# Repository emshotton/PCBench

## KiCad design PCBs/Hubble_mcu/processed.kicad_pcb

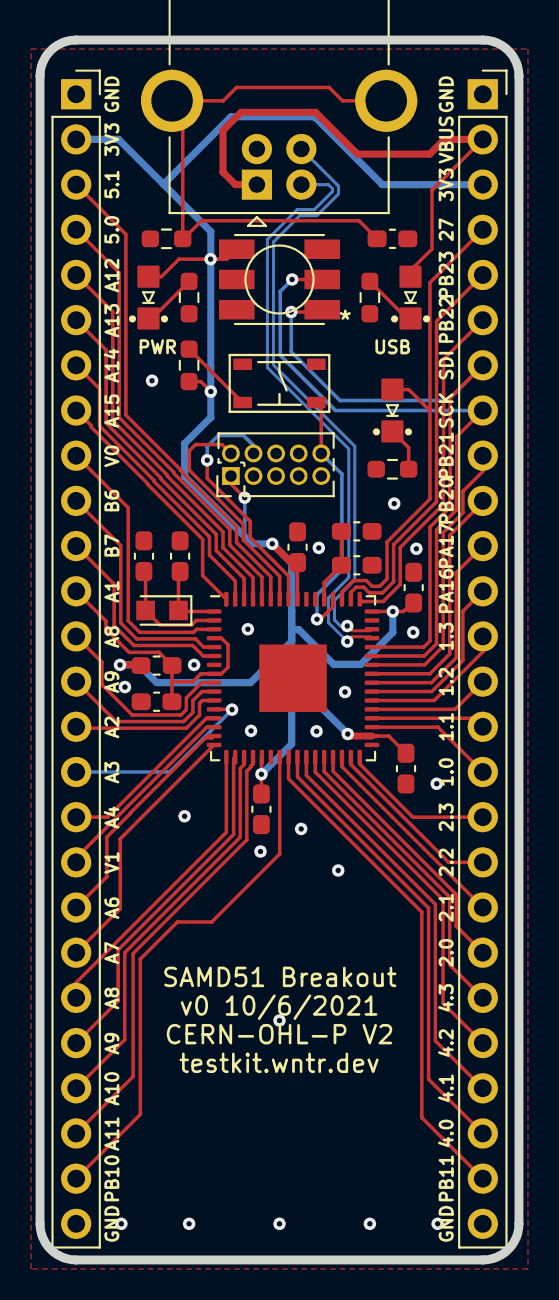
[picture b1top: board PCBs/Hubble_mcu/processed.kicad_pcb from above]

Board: 2 copper layers, 26.9 x 68.6 mm, 27 parts (0 on the bottom side), 60 nets.

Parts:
C1, C2: 18pF; C_0603_1608Metric_Pad1.08x0.95mm_HandSolder
C3: 4.7nF; C_0603_1608Metric_Pad1.08x0.95mm_HandSolder
C4, C5, C7, C8, C9, C10: 0.1uF; C_0603_1608Metric_Pad1.08x0.95mm_HandSolder
C6: 4.7uF; C_0603_1608Metric_Pad1.08x0.95mm_HandSolder
D1: POWER; LED_0805_Kingbright_APT2012
D2: USB; LED_0805_Kingbright_APT2012
D3: Dotstar; Dotstar_5050
D4: ACT; LED_0805_Kingbright_APT2012
FB1: 300mA; L_0603_1608Metric_Pad1.05x0.95mm_HandSolder
J1: USB_B_Receptacle; USB_B_OST_USB-B1HSxx_Horizontal
J2: SWD; PinHeader_2x05_P1.27mm_Vertical
J3, J4: Conn_01x26; PinSocket_1x26_P2.54mm_Vertical
R1, R2, R3, R4, R5: 10k; R_0603_1608Metric_Pad0.98x0.95mm_HandSolder
SW1: RESET; Tactile_Switch_4.2mm
U2: ATSAMD51J20A-M; QFN-64-1EP_9x9mm_P0.5mm_EP3.8x3.8mm
Y1: 32.768kHz; Crystal_SMD_2012-2Pin_2.0x1.2mm_HandSoldering

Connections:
+3V3: C7.1, C8.1, C9.1, C10.1, D1.2, D3.4, FB1.2, J2.1, J3.2, J4.3, R3.1, U2.21, U2.34, U2.48, U2.56
/ADC0.AIN1+ANAREF.VREF0: C4.1, FB1.1, J3.12, U2.4, U2.8
/ADC0.AIN2+ADC1.AIN0: J3.15, U2.11
/ADC0.AIN3+ADC1.AIN1: J3.16, U2.12
/ADC0.AIN4+ANAREF.VREF1: J3.17, U2.13
/ADC0.AIN6+ANAREF.VREF2: J3.19, U2.15
/ADC0.AIN7: J3.20, U2.16
/ADC0.AIN8+ADC1.AIN2: J3.21, U2.17
/ADC0.AIN9+ADC1.AIN3: J3.22, U2.18
/ADC0.AIN10: J3.23, U2.19
/ADC0.AIN11: J3.24, U2.20
/ADC0.AIN12: J3.5, U2.61
/ADC0.AIN13: J3.6, U2.62
/ADC0.AIN14: J3.7, U2.63
/ADC0.AIN15: J3.8, U2.64
/ADC1.AIN6: J3.10, U2.5
/ADC1.AIN7: J3.11, U2.6
/ADC1.AIN8: J3.13, U2.9
/ADC1.AIN9: J3.14, U2.10
/D+: J1.3, U2.46
/D-: J1.2, U2.45
/DAC.VOUT0: J3.9, U2.3
/DAC.VOUT1: J3.18, U2.14
/DOTSTAR_SCK: D3.2, J4.8, U2.43
/DOTSTAR_SDI: D3.1, J4.7, U2.44
/PA16: J4.12, U2.39
/PA17: J4.11, U2.40
/PA20: J4.10, U2.41
/PA21: J4.9, U2.42
/PA27: D4.2, J4.4, U2.51
/PB10: J3.25, U2.23
/PB11: J4.25, U2.24
/PB22: J4.6, U2.49
/PB23: J4.5, U2.50
/RESET: J2.10, R3.2, SW1.1, U2.52
/SERCOM1.0: J4.16, U2.35
/SERCOM1.1: J4.15, U2.36
/SERCOM1.2: J4.14, U2.37
/SERCOM1.3: J4.13, U2.38
/SERCOM2.0: J4.20, U2.29
/SERCOM2.1: J4.19, U2.30
/SERCOM2.2: J4.18, U2.31
/SERCOM2.3: J4.17, U2.32
/SERCOM4.0: J4.24, U2.25
/SERCOM4.1: J4.23, U2.26
/SERCOM4.2: J4.22, U2.27
/SERCOM4.3: J4.21, U2.28
/SERCOM5.0: J3.4, U2.60
/SERCOM5.1: J3.3, U2.59
/SWCLK: J2.4, U2.57
/SWDIO: J2.2, U2.58
/VBUS: D2.2, J1.1, J4.2
/VDDCORE: C5.1, C6.1, U2.53
/XIN: C1.1, U2.1, Y1.1
/XOUT: C2.1, U2.2, Y1.2
GND: C1.2, C2.2, C3.2, C4.2, C5.2, C6.2, C7.2, C8.2, C9.2, C10.2, D3.3, J1.4, J2.3, J2.5, J2.9, J3.1, J3.26, J4.1, J4.26, R1.2, R2.2, R4.2, R5.2, SW1.2, U2.7, U2.22, U2.33, U2.47, U2.54, U2.65
unnamed: C3.1, J1.5, R4.1
unnamed: D1.1, R1.1
unnamed: D2.1, R2.1
unnamed: D4.1, R5.1

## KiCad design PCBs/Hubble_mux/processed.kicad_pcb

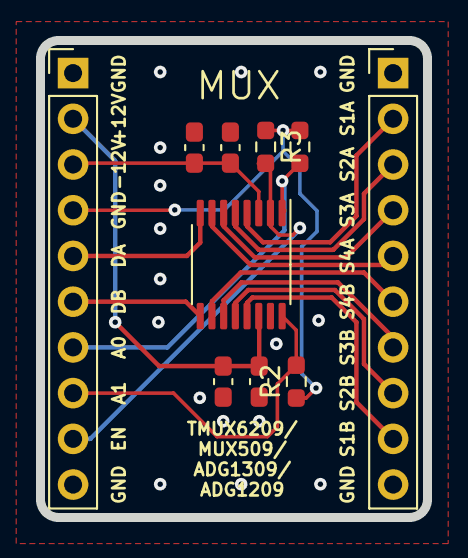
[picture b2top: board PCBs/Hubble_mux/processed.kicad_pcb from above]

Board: 2 copper layers, 21.5 x 26.5 mm, 10 parts (0 on the bottom side), 17 nets.

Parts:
C1, C3: 1uF; C_0603_1608Metric_Pad1.08x0.95mm_HandSolder
C2, C4: 0.1uF; C_0603_1608Metric_Pad1.08x0.95mm_HandSolder
J1: Left; PinHeader_1x10_P2.54mm_Vertical
J2: Right; PinHeader_1x10_P2.54mm_Vertical
R1, R2, R3: 10k; R_0603_1608Metric_Pad0.98x0.95mm_HandSolder
U1: TMUX6209; TSSOP-16_4.4x5mm_P0.65mm

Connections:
+3V3: J1.4, R1.1, R2.1, R3.1
+12V: C1.1, C2.1, J1.2, U1.14
-12V: C3.1, C4.1, J1.3, U1.3
/A0: J1.7, R1.2, U1.1
/A1: J1.8, R2.2, U1.16
/DA: J1.5, U1.8
/DB: J1.6, U1.9
/EN: J1.9, R3.2, U1.2
/S1A: J2.2, U1.4
/S1B: J2.9, U1.13
/S2A: J2.3, U1.5
/S2B: J2.8, U1.12
/S3A: J2.4, U1.6
/S3B: J2.7, U1.11
/S4A: J2.5, U1.7
/S4B: J2.6, U1.10
GND: C1.2, C2.2, C3.2, C4.2, J1.1, J1.10, J2.1, J2.10, U1.15

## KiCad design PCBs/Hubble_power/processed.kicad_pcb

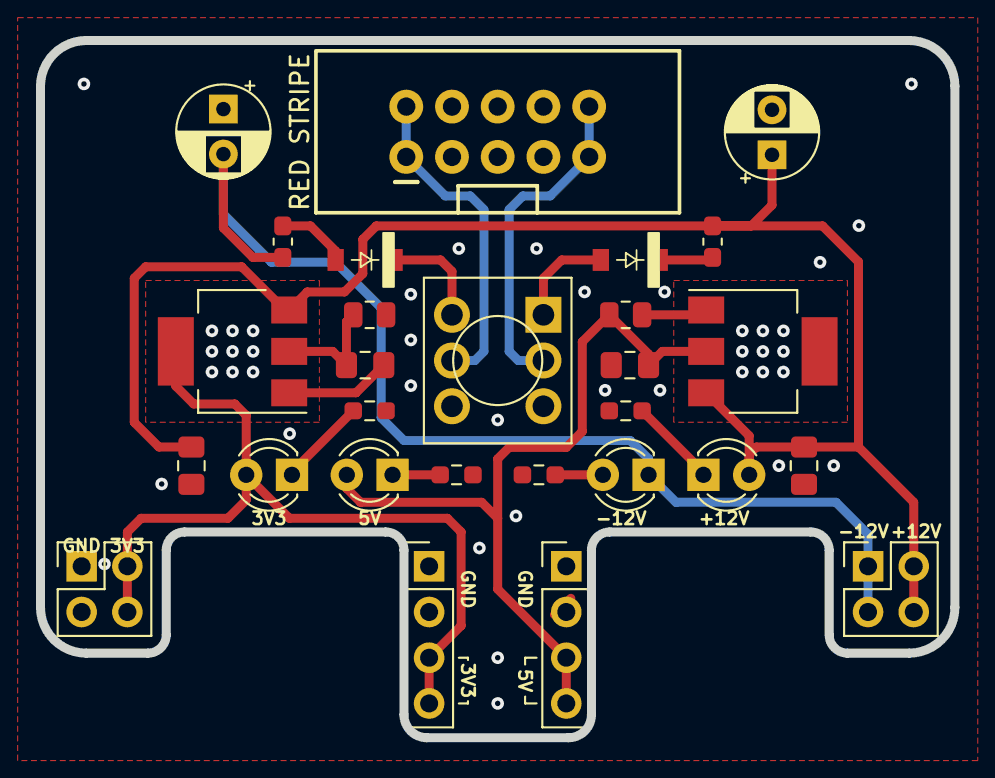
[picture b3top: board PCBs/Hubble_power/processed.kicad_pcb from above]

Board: 2 copper layers, 50.8 x 38.7 mm, 28 parts (0 on the bottom side), 15 nets.

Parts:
C1, C2, C3, C4: 10uF; C_0805_2012Metric_Pad1.18x1.45mm_HandSolder
C5, C6: 10uF; CP_Radial_D5.0mm_P2.50mm
D1, D2: BARRIER; D_SOD-123
D3: Blue; LED_D3.0mm
D4: Red; LED_D3.0mm
D5: Green; LED_D3.0mm
D6: Yellow; LED_D3.0mm
FB1, FB2: BEAD; L_0603_1608Metric_Pad1.05x0.95mm_HandSolder
J1: Eurorack_Power
J2: Left power; PinHeader_2x02_P2.54mm_Vertical
J3: Left; PinHeader_1x04_P2.54mm_Vertical
J4: Right; PinHeader_1x04_P2.54mm_Vertical
J5: Right power; PinHeader_2x02_P2.54mm_Vertical
R1, R2: 0.3-22R; R_0805_2012Metric
R3, R4, R5, R6: 1k; R_0603_1608Metric_Pad0.98x0.95mm_HandSolder
SW1: Power; Switch_DPDT_Thonk_DW4_2.54mm_pitch_5.08mm_spacing
U1: LM1117-3.3; SOT-223-3_TabPin2
U2: LM1117-5.0; SOT-223-3_TabPin2

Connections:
+3V3: C3.1, D5.2, J2.2, J2.4, J3.3, J3.4, R1.1, U1.2
+5V: C4.1, D6.2, J4.3, J4.4, R2.1, U2.2
+12V: C1.2, C2.2, C5.1, D3.2, FB1.1, J5.2, J5.4, U1.3, U2.3
-12V: C6.2, D4.1, FB2.1, J5.1, J5.3
/+12VRAW: J1.9, J1.10, SW1.2
/+12VSWITCHED: D1.2, SW1.1
/-12VRAW: J1.1, J1.2, SW1.5
/-12VSWITCHED: D2.1, SW1.4
GND: C1.1, C2.1, C3.2, C4.2, C5.2, C6.1, J1.3, J1.4, J1.5, J1.6, J1.7, J1.8, J2.1, J2.3, J3.1, J3.2, J4.1, J4.2, R1.2, R2.2, R3.2, R4.2, R5.2, R6.2, U1.1, U2.1
unnamed: D1.1, FB1.2
unnamed: D2.2, FB2.2
unnamed: D3.1, R3.1
unnamed: D4.2, R4.1
unnamed: D5.1, R5.1
unnamed: D6.1, R6.1

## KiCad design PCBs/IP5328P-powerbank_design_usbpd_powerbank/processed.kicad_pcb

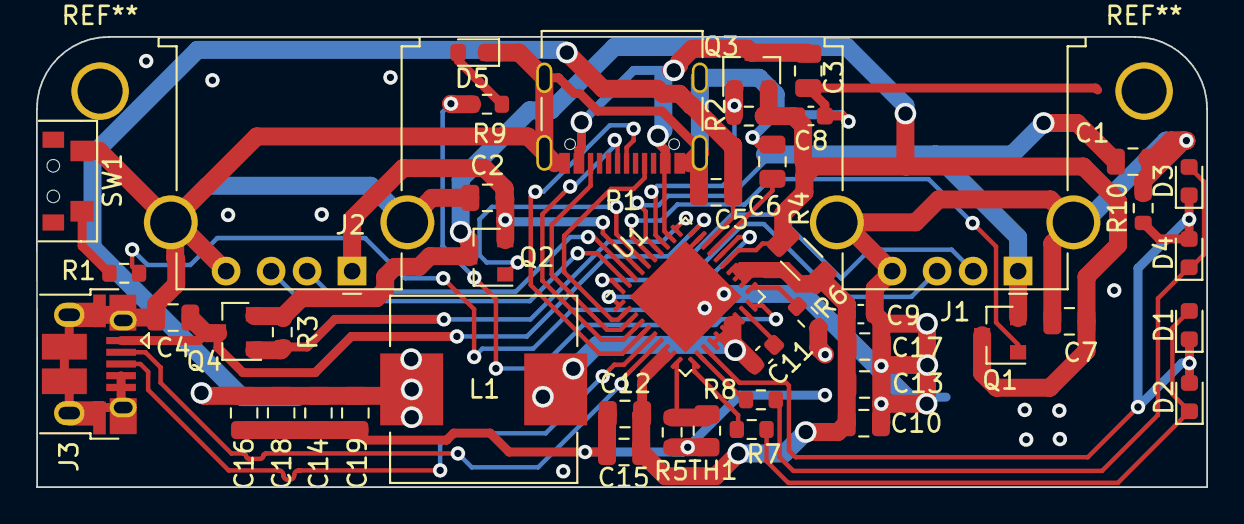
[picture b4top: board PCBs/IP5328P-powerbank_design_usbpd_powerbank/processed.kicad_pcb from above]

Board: 2 copper layers, 65.0 x 25.0 mm, 47 parts (1 on the bottom side), 36 nets.

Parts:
BT1: Battery_Cell; bat
C1, C2, C3, C4, C17: 10uf 25v; C_0805_2012Metric
C5, C6: 2.2uf 16v; C_0805_2012Metric
C7, C10, C12, C13, C15: 22uf 25v; C_0805_2012Metric
C8, C9, C11: 100nf 25v; C_0603_1608Metric
C14, C16, C18, C19: 22uf 16v; C_0805_2012Metric
D1, D2, D3, D4, D5: LED; LED_0603_1608Metric
J1, J2: USB_A; USB_A_Stewart_SS-52100-001_Horizontal
J3: USB_B_Micro; USB_Micro-B_Amphenol_10103594-0001LF_Horizontal
L1: 2.2uh; L_Wuerth_HCI-1040
P1: USB_C_Plug_USB2.0; USB_C_Receptacle_Palconn_UTC16-G
Q1, Q2: RU207C; SOT-23
Q3, Q4: RU20P7C; SOT-23
R1: 1k; R_0603_1608Metric
R2, R3: 10k; R_0603_1608Metric
R4: 0.01R; R_1206_3216Metric
R5: 82k 1%; R_0603_1608Metric
R6: 114k; R_0603_1608Metric
R7, R8, R9: 100R; R_0603_1608Metric
R10: NC; R_0603_1608Metric
SW1: SW_Push; FPC_2
TH1: 100k@25c; R_0805_2012Metric
U1: IP5328; QFN-40-1EP_6x6mm_P0.5mm_EP4.6x4.6mm

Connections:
/CC1: P1.A5 (CC), U1.2 (CC1)
/CC2: P1.B5 (VCONN), U1.3 (CC2)
/DMA1: J2.2 (D-), U1.38 (DMA1)
/DMA2: J1.2 (D-), U1.40 (DMA2)
/DMB: J3.3 (D+), U1.6 (DMB)
/DMC: P1.A7 (D-), U1.4 (DMC)
/DPA1: J2.3 (D+), U1.39 (DPA1)
/DPA2: J1.3 (D+), U1.1 (DPA2)
/DPB: J3.2 (D-), U1.7 (DPB)
/DPC: P1.A6 (D+), U1.5 (DPC)
/KEY: R1.1, U1.26 (KEY)
/LIGHT: R9.1, U1.20 (LIGHT)
/VBAT: BT1.1 (+), C5.1, C14.1, C16.1, C18.1, C19.1, L1.2, U1.28 (BAT)
/VBUS: C3.1, P1.A4 (VBUS), P1.A9 (VBUS), P1.B4 (VBUS), P1.B9 (VBUS), Q3.3 (D), U1.32 (VBUS)
/VBUSG: Q3.1 (G), R2.2, U1.33 (VBUSG)
/VIN: C4.1, J3.1 (VBUS), Q4.3 (D), U1.30 (VIN)
/VING: Q4.1 (G), R3.2, U1.31 (VING)
/VMID: C7.1, C8.1, Q1.3 (D), Q2.3 (D), Q3.2 (S), Q4.2 (S), R2.1, R3.1, R4.1, U1.25 (VSN)
/VOUT1: C2.1, J2.1 (VBUS), Q2.2 (S), U1.37 (VOUT1)
/VOUT1G: Q2.1 (G), U1.36 (VOUT1G)
/VOUT2: C1.1, J1.1 (VBUS), Q1.2 (S), U1.34 (VOUT2)
/VOUT2G: Q1.1 (G), U1.35 (VOUT2G)
/VREG: C6.1, U1.27 (VREG)
/VSYS: C9.2, C10.1, C12.1, C13.1, C15.1, C17.1, R4.2, U1.8 (VSYS), U1.9 (VSYS), U1.22 (VSYS), U1.23 (VSYS), U1.24 (VSP)
GND: BT1.2 (-), C1.2, C2.2, C3.2, C4.2, C5.2, C6.2, C7.2, C8.2, C9.1, C10.2, C12.2, C13.2, C14.2, C15.2, C16.2, C17.2, C18.2, C19.2, D5.1 (K), J1.4 (GND), J1.5 (Shield), J2.4 (GND), J2.5 (Shield), J3.4 (ID), J3.5 (GND), J3.6 (Shield), P1.A1 (GND), P1.A12 (GND), P1.B1 (GND), P1.B12 (GND), P1.S1 (SHIELD), R5.2, R6.2, R10.2, SW1.2, TH1.2, U1.29 (AGND), U1.41 (EPAD)
unnamed: C11.1, U1.19 (BST)
unnamed: C11.2, L1.1, U1.14 (LX), U1.15 (LX), U1.16 (LX), U1.17 (LX), U1.18 (LX)
unnamed: D1.1 (K), D2.2 (A), D3.1 (K), D4.2 (A), R10.1, U1.13 (L3)
unnamed: D1.2 (A), D2.1 (K), R7.2
unnamed: D3.2 (A), D4.1 (K), R8.2
unnamed: D5.2 (A), R9.2
unnamed: R1.2, SW1.1
unnamed: R5.1, TH1.1, U1.10 (NTC)
unnamed: R6.1, U1.21 (RSET)
unnamed: R7.1, U1.11 (L1)
unnamed: R8.1, U1.12 (L2)

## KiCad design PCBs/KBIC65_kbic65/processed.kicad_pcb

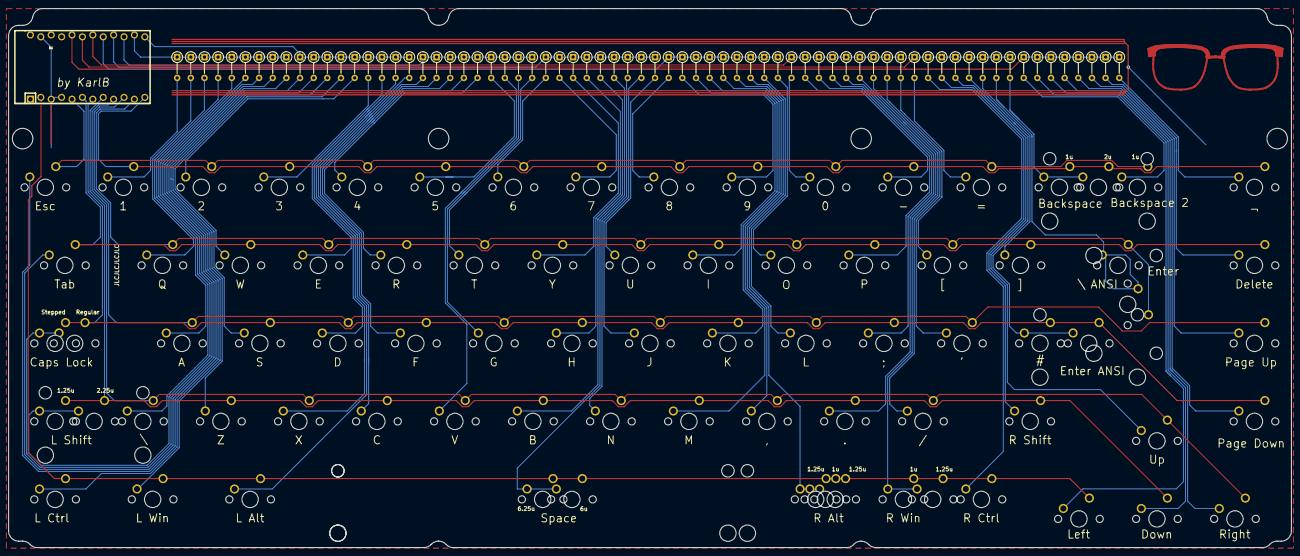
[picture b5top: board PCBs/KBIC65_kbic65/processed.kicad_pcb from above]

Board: 2 copper layers, 313.3 x 131.6 mm, 150 parts (0 on the bottom side), 88 nets.

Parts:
D_0, D_1, D_2, D_3, D_4, D_5, D_6, D_7, D_8, D_9: SOD_123; D_DO-35_SOD27_P5.08mm_Vertical_AnodeUp
D_@1: SOD_123; D_DO-35_SOD27_P5.08mm_Vertical_AnodeUp
D_A1: SOD_123; D_DO-35_SOD27_P5.08mm_Vertical_AnodeUp
D_B1: SOD_123; D_DO-35_SOD27_P5.08mm_Vertical_AnodeUp
D_BKSLSH1: SOD_123; D_DO-35_SOD27_P5.08mm_Vertical_AnodeUp
D_BkSp1, D_BkSp2: SOD_123; D_DO-35_SOD27_P5.08mm_Vertical_AnodeUp
D_C1: SOD_123; D_DO-35_SOD27_P5.08mm_Vertical_AnodeUp
D_Comma1: SOD_123; D_DO-35_SOD27_P5.08mm_Vertical_AnodeUp
D_CpsLck1: SOD_123; D_DO-35_SOD27_P5.08mm_Vertical_AnodeUp
D_D1: SOD_123; D_DO-35_SOD27_P5.08mm_Vertical_AnodeUp
D_Del1: SOD_123; D_DO-35_SOD27_P5.08mm_Vertical_AnodeUp
D_Dot1: SOD_123; D_DO-35_SOD27_P5.08mm_Vertical_AnodeUp
D_Down1: SOD_123; D_DO-35_SOD27_P5.08mm_Vertical_AnodeUp
D_E1: SOD_123; D_DO-35_SOD27_P5.08mm_Vertical_AnodeUp
D_Enter1: SOD_123; D_DO-35_SOD27_P5.08mm_Vertical_AnodeUp
D_Equal1: SOD_123; D_DO-35_SOD27_P5.08mm_Vertical_AnodeUp
D_Esc1: SOD_123; D_DO-35_SOD27_P5.08mm_Vertical_AnodeUp
D_F1: SOD_123; D_DO-35_SOD27_P5.08mm_Vertical_AnodeUp
D_FwdSlsh1: SOD_123; D_DO-35_SOD27_P5.08mm_Vertical_AnodeUp
D_G1: SOD_123; D_DO-35_SOD27_P5.08mm_Vertical_AnodeUp
D_H1: SOD_123; D_DO-35_SOD27_P5.08mm_Vertical_AnodeUp
D_Hyphen1: SOD_123; D_DO-35_SOD27_P5.08mm_Vertical_AnodeUp
D_I1: SOD_123; D_DO-35_SOD27_P5.08mm_Vertical_AnodeUp
D_ISO_BKSLSH1: SOD_123; D_DO-35_SOD27_P5.08mm_Vertical_AnodeUp
D_J1: SOD_123; D_DO-35_SOD27_P5.08mm_Vertical_AnodeUp
D_K1: SOD_123; D_DO-35_SOD27_P5.08mm_Vertical_AnodeUp
D_L1: SOD_123; D_DO-35_SOD27_P5.08mm_Vertical_AnodeUp
D_LAlt1: SOD_123; D_DO-35_SOD27_P5.08mm_Vertical_AnodeUp
D_LBKT1: SOD_123; D_DO-35_SOD27_P5.08mm_Vertical_AnodeUp
D_LCtrl1: SOD_123; D_DO-35_SOD27_P5.08mm_Vertical_AnodeUp
D_LShift1: SOD_123; D_DO-35_SOD27_P5.08mm_Vertical_AnodeUp
D_LWin1: SOD_123; D_DO-35_SOD27_P5.08mm_Vertical_AnodeUp
D_Left1: SOD_123; D_DO-35_SOD27_P5.08mm_Vertical_AnodeUp
D_M1: SOD_123; D_DO-35_SOD27_P5.08mm_Vertical_AnodeUp
D_N1: SOD_123; D_DO-35_SOD27_P5.08mm_Vertical_AnodeUp
D_O1: SOD_123; D_DO-35_SOD27_P5.08mm_Vertical_AnodeUp
D_P1: SOD_123; D_DO-35_SOD27_P5.08mm_Vertical_AnodeUp
D_PgDn1: SOD_123; D_DO-35_SOD27_P5.08mm_Vertical_AnodeUp
D_PgUp1: SOD_123; D_DO-35_SOD27_P5.08mm_Vertical_AnodeUp
D_Q1: SOD_123; D_DO-35_SOD27_P5.08mm_Vertical_AnodeUp
D_R1: SOD_123; D_DO-35_SOD27_P5.08mm_Vertical_AnodeUp
D_RAlt1: SOD_123; D_DO-35_SOD27_P5.08mm_Vertical_AnodeUp
D_RBKT1: SOD_123; D_DO-35_SOD27_P5.08mm_Vertical_AnodeUp
D_RCtrl1: SOD_123; D_DO-35_SOD27_P5.08mm_Vertical_AnodeUp
D_RShift1: SOD_123; D_DO-35_SOD27_P5.08mm_Vertical_AnodeUp
D_RWin1: SOD_123; D_DO-35_SOD27_P5.08mm_Vertical_AnodeUp
D_Right1: SOD_123; D_DO-35_SOD27_P5.08mm_Vertical_AnodeUp
D_S1: SOD_123; D_DO-35_SOD27_P5.08mm_Vertical_AnodeUp
D_SemiCol1: SOD_123; D_DO-35_SOD27_P5.08mm_Vertical_AnodeUp
D_Space1: SOD_123; D_DO-35_SOD27_P5.08mm_Vertical_AnodeUp
D_T1: SOD_123; D_DO-35_SOD27_P5.08mm_Vertical_AnodeUp
D_Tab1: SOD_123; D_DO-35_SOD27_P5.08mm_Vertical_AnodeUp
D_Tilde1: SOD_123; D_DO-35_SOD27_P5.08mm_Vertical_AnodeUp
D_U1: SOD_123; D_DO-35_SOD27_P5.08mm_Vertical_AnodeUp
D_Up1: SOD_123; D_DO-35_SOD27_P5.08mm_Vertical_AnodeUp
D_V1: SOD_123; D_DO-35_SOD27_P5.08mm_Vertical_AnodeUp
D_W1: SOD_123; D_DO-35_SOD27_P5.08mm_Vertical_AnodeUp
D_X1: SOD_123; D_DO-35_SOD27_P5.08mm_Vertical_AnodeUp
D_Y1: SOD_123; D_DO-35_SOD27_P5.08mm_Vertical_AnodeUp
D_Z1: SOD_123; D_DO-35_SOD27_P5.08mm_Vertical_AnodeUp
MX_0, MX_1, MX_2, MX_3, MX_4, MX_5, MX_6, MX_7, MX_8, MX_9: MX-NoLED; MXOnly-1U-NoLED
MX_@1: MX-NoLED; MXOnly-1U-NoLED
MX_A1: MX-NoLED; MXOnly-1U-NoLED
MX_B1: MX-NoLED; MXOnly-1U-NoLED
MX_BkSlash2_ISO_Enter1: MX-NoLED; MXOnly-ISO-ROTATED-ReversedStabilizers-NoLED
MX_BkSlsh1: MX-NoLED; MXOnly-1.5U-NoLED
MX_BkSp1, MX_BkSp2: MX-NoLED; MXOnly-1U-NoLED
MX_BkSp3_2u1: MX-NoLED; MXOnly-2U-NoLED
MX_C1: MX-NoLED; MXOnly-1U-NoLED
MX_Comma1: MX-NoLED; MXOnly-1U-NoLED
MX_CpsLck1: MX-NoLED; MXOnly-1.75U-NoLED
MX_CpsLck2_Stepped1: MX-NoLED; MXOnly-1.25U-NoLED
MX_D1: MX-NoLED; MXOnly-1U-NoLED
MX_Del1: MX-NoLED; MXOnly-1U-NoLED
MX_Dot1: MX-NoLED; MXOnly-1U-NoLED
MX_Down1: MX-NoLED; MXOnly-1U-NoLED
MX_E1: MX-NoLED; MXOnly-1U-NoLED
MX_Enter1: MX-NoLED; MXOnly-2.25U-NoLED
MX_Enter2_ISO_Hash1: MX-NoLED; MXOnly-1U-NoLED
MX_Equal1: MX-NoLED; MXOnly-1U-NoLED
MX_Esc1: MX-NoLED; MXOnly-1U-NoLED
MX_F1: MX-NoLED; MXOnly-1U-NoLED
MX_FwdSlsh1: MX-NoLED; MXOnly-1U-NoLED
MX_G1: MX-NoLED; MXOnly-1U-NoLED
MX_H1: MX-NoLED; MXOnly-1U-NoLED
MX_Hyphen1: MX-NoLED; MXOnly-1U-NoLED
MX_I1: MX-NoLED; MXOnly-1U-NoLED
MX_ISO_BKSLSH1: MX-NoLED; MXOnly-1U-NoLED
MX_J1: MX-NoLED; MXOnly-1U-NoLED
MX_K1: MX-NoLED; MXOnly-1U-NoLED
MX_L1: MX-NoLED; MXOnly-1U-NoLED
MX_LAlt1: MX-NoLED; MXOnly-1.25U-NoLED
MX_LBKT1: MX-NoLED; MXOnly-1U-NoLED
MX_LCtrl1: MX-NoLED; MXOnly-1.25U-NoLED
MX_LShift_ANSI1: MX-NoLED; MXOnly-2.25U-NoLED
MX_LShift_ISO1: MX-NoLED; MXOnly-1.25U-NoLED
MX_LWin1: MX-NoLED; MXOnly-1.25U-NoLED
MX_Left1: MX-NoLED; MXOnly-1U-NoLED
MX_M1: MX-NoLED; MXOnly-1U-NoLED
MX_N1: MX-NoLED; MXOnly-1U-NoLED
MX_O1: MX-NoLED; MXOnly-1U-NoLED
MX_P1: MX-NoLED; MXOnly-1U-NoLED
MX_PgDn1: MX-NoLED; MXOnly-1U-NoLED
MX_PgUp1: MX-NoLED; MXOnly-1U-NoLED
MX_Q1: MX-NoLED; MXOnly-1U-NoLED
MX_R1: MX-NoLED; MXOnly-1U-NoLED
MX_RAlt1_1u1: MX-NoLED; MXOnly-1U-NoLED
MX_RAlt2_1.25u_6u_space1, MX_RAlt3_1.25u_6.25u_space1: MX-NoLED; MXOnly-1.25U-NoLED
MX_RBKT1: MX-NoLED; MXOnly-1U-NoLED
MX_RCtrl1: MX-NoLED; MXOnly-1U-NoLED
MX_RShift1: MX-NoLED; MXOnly-1.75U-NoLED
MX_RWin1, MX_RWin2_1.25u_RCtrl1: MX-NoLED; MXOnly-1U-NoLED
MX_Right1: MX-NoLED; MXOnly-1U-NoLED
MX_S1: MX-NoLED; MXOnly-1U-NoLED
MX_SemiCol1: MX-NoLED; MXOnly-1U-NoLED
MX_Space1_6.25u1: MX-NoLED; MXOnly-6.25U-NoLED
MX_Space2_6u1: MX-NoLED; MXOnly-6U-NoLED
MX_T1: MX-NoLED; MXOnly-1U-NoLED
MX_Tab1: MX-NoLED; MXOnly-1.5U-NoLED
MX_Tilde1: MX-NoLED; MXOnly-1U-NoLED
MX_U1: MX-NoLED; MXOnly-1U-NoLED
MX_Up1: MX-NoLED; MXOnly-1U-NoLED
MX_V1: MX-NoLED; MXOnly-1U-NoLED
MX_W1: MX-NoLED; MXOnly-1U-NoLED
MX_X1: MX-NoLED; MXOnly-1U-NoLED
MX_Y1: MX-NoLED; MXOnly-1U-NoLED
MX_Z1: MX-NoLED; MXOnly-1U-NoLED
U1: ProMicro; ArduinoProMicro-ZigZag

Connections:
COL0: D_1.1, D_A1.1, D_CpsLck1.1, D_Esc1.1, D_ISO_BKSLSH1.1, D_LCtrl1.1, D_LShift1.1, D_Q1.1, D_Tab1.1, U1.14
COL1: D_2.1, D_3.1, D_D1.1, D_E1.1, D_LWin1.1, D_S1.1, D_W1.1, D_X1.1, D_Z1.1, U1.13
COL2: D_4.1, D_5.1, D_C1.1, D_F1.1, D_G1.1, D_LAlt1.1, D_R1.1, D_T1.1, D_V1.1, U1.15
COL3: D_6.1, D_7.1, D_B1.1, D_H1.1, D_J1.1, D_N1.1, D_Space1.1, D_U1.1, D_Y1.1, U1.16
COL4: D_8.1, D_9.1, D_Comma1.1, D_I1.1, D_K1.1, D_L1.1, D_M1.1, D_O1.1, D_RAlt1.1, U1.17
COL5: D_0.1, D_@1.1, D_Dot1.1, D_FwdSlsh1.1, D_Hyphen1.1, D_LBKT1.1, D_P1.1, D_RWin1.1, D_SemiCol1.1, U1.18
COL6: D_BKSLSH1.1, D_BkSp1.1, D_Enter1.1, D_Equal1.1, D_RBKT1.1, D_RCtrl1.1, D_RShift1.1, D_Up1.1, U1.19
COL7: D_BkSp2.1, D_Del1.1, D_Down1.1, D_Left1.1, D_PgDn1.1, D_PgUp1.1, D_Right1.1, D_Tilde1.1, U1.20
GND: U1.3, U1.4, U1.23
unnamed: D_0.2, MX_0.1
unnamed: D_1.2, MX_1.1
unnamed: D_2.2, MX_2.1
unnamed: D_3.2, MX_3.1
unnamed: D_4.2, MX_4.1
unnamed: D_5.2, MX_5.1
unnamed: D_6.2, MX_6.1
unnamed: D_7.2, MX_7.1
unnamed: D_8.2, MX_8.1
unnamed: D_9.2, MX_9.1
unnamed: D_@1.2, MX_@1.1
unnamed: D_A1.2, MX_A1.1
unnamed: D_B1.2, MX_B1.1
unnamed: D_BKSLSH1.2, MX_BkSlash2_ISO_Enter1.1, MX_BkSlsh1.1
unnamed: D_BkSp1.2, MX_BkSp1.1, MX_BkSp3_2u1.1
unnamed: D_BkSp2.2, MX_BkSp2.1
unnamed: D_C1.2, MX_C1.1
unnamed: D_Comma1.2, MX_Comma1.1
unnamed: D_CpsLck1.2, MX_CpsLck1.1, MX_CpsLck2_Stepped1.1
unnamed: D_D1.2, MX_D1.1
unnamed: D_Del1.2, MX_Del1.1
unnamed: D_Dot1.2, MX_Dot1.1
unnamed: D_Down1.2, MX_Down1.1
unnamed: D_E1.2, MX_E1.1
unnamed: D_Enter1.2, MX_Enter1.1, MX_Enter2_ISO_Hash1.1
unnamed: D_Equal1.2, MX_Equal1.1
unnamed: D_Esc1.2, MX_Esc1.1
unnamed: D_F1.2, MX_F1.1
unnamed: D_FwdSlsh1.2, MX_FwdSlsh1.1
unnamed: D_G1.2, MX_G1.1
unnamed: D_H1.2, MX_H1.1
unnamed: D_Hyphen1.2, MX_Hyphen1.1
unnamed: D_I1.2, MX_I1.1
unnamed: D_ISO_BKSLSH1.2, MX_ISO_BKSLSH1.1
unnamed: D_J1.2, MX_J1.1
unnamed: D_K1.2, MX_K1.1
unnamed: D_L1.2, MX_L1.1
unnamed: D_LAlt1.2, MX_LAlt1.1
unnamed: D_LBKT1.2, MX_LBKT1.1
unnamed: D_LCtrl1.2, MX_LCtrl1.1
unnamed: D_LShift1.2, MX_LShift_ANSI1.1, MX_LShift_ISO1.1
unnamed: D_LWin1.2, MX_LWin1.1
unnamed: D_Left1.2, MX_Left1.1
unnamed: D_M1.2, MX_M1.1
unnamed: D_N1.2, MX_N1.1
unnamed: D_O1.2, MX_O1.1
unnamed: D_P1.2, MX_P1.1
unnamed: D_PgDn1.2, MX_PgDn1.1
unnamed: D_PgUp1.2, MX_PgUp1.1
unnamed: D_Q1.2, MX_Q1.1
unnamed: D_R1.2, MX_R1.1
unnamed: D_RAlt1.2, MX_RAlt1_1u1.1, MX_RAlt2_1.25u_6u_space1.1, MX_RAlt3_1.25u_6.25u_space1.1
unnamed: D_RBKT1.2, MX_RBKT1.1
unnamed: D_RCtrl1.2, MX_RCtrl1.1
unnamed: D_RShift1.2, MX_RShift1.1
unnamed: D_RWin1.2, MX_RWin1.1, MX_RWin2_1.25u_RCtrl1.1
unnamed: D_Right1.2, MX_Right1.1
unnamed: D_S1.2, MX_S1.1
unnamed: D_SemiCol1.2, MX_SemiCol1.1
unnamed: D_Space1.2, MX_Space1_6.25u1.1, MX_Space2_6u1.1
unnamed: D_T1.2, MX_T1.1
unnamed: D_Tab1.2, MX_Tab1.1
unnamed: D_Tilde1.2, MX_Tilde1.1
unnamed: D_U1.2, MX_U1.1
unnamed: D_Up1.2, MX_Up1.1
unnamed: D_V1.2, MX_V1.1
unnamed: D_W1.2, MX_W1.1
unnamed: D_X1.2, MX_X1.1
unnamed: D_Y1.2, MX_Y1.1
unnamed: D_Z1.2, MX_Z1.1
ROW0: MX_1.2, MX_3.2, MX_5.2, MX_7.2, MX_9.2, MX_BkSp1.2, MX_BkSp3_2u1.2, MX_Hyphen1.2, MX_Tilde1.2, U1.12
ROW1: MX_0.2, MX_2.2, MX_4.2, MX_6.2, MX_8.2, MX_BkSp2.2, MX_Equal1.2, MX_Esc1.2, U1.5
ROW2: MX_BkSlash2_ISO_Enter1.2, MX_BkSlsh1.2, MX_E1.2, MX_LBKT1.2, MX_O1.2, MX_Q1.2, MX_T1.2, MX_U1.2, U1.11
ROW3: MX_Del1.2, MX_I1.2, MX_P1.2, MX_R1.2, MX_RBKT1.2, MX_Tab1.2, MX_W1.2, MX_Y1.2, U1.6
ROW4: MX_@1.2, MX_A1.2, MX_D1.2, MX_G1.2, MX_J1.2, MX_L1.2, MX_PgUp1.2, U1.10
ROW5: MX_CpsLck1.2, MX_CpsLck2_Stepped1.2, MX_Enter1.2, MX_Enter2_ISO_Hash1.2, MX_F1.2, MX_H1.2, MX_K1.2, MX_PgDn1.2, MX_S1.2, MX_SemiCol1.2, U1.7
ROW6: MX_Comma1.2, MX_FwdSlsh1.2, MX_ISO_BKSLSH1.2, MX_N1.2, MX_Right1.2, MX_Up1.2, MX_V1.2, MX_X1.2, U1.9
ROW7: MX_B1.2, MX_C1.2, MX_Dot1.2, MX_Down1.2, MX_LShift_ANSI1.2, MX_LShift_ISO1.2, MX_M1.2, MX_RShift1.2, MX_Z1.2, U1.8
ROW8: MX_LAlt1.2, MX_LCtrl1.2, MX_LWin1.2, MX_Left1.2, MX_RAlt1_1u1.2, MX_RAlt2_1.25u_6u_space1.2, MX_RAlt3_1.25u_6.25u_space1.2, MX_RCtrl1.2, MX_RWin1.2, MX_RWin2_1.25u_RCtrl1.2, MX_Space1_6.25u1.2, MX_Space2_6u1.2, U1.2

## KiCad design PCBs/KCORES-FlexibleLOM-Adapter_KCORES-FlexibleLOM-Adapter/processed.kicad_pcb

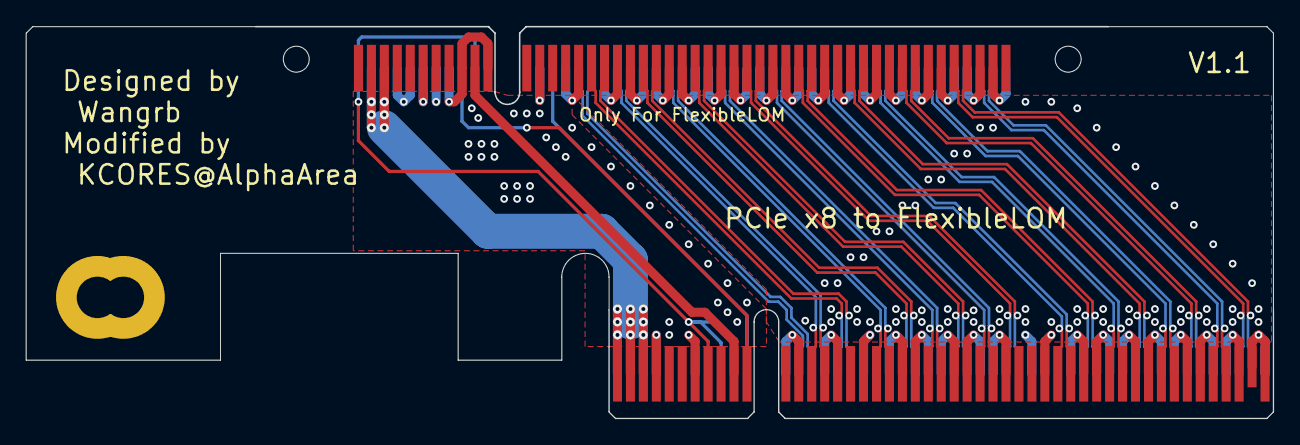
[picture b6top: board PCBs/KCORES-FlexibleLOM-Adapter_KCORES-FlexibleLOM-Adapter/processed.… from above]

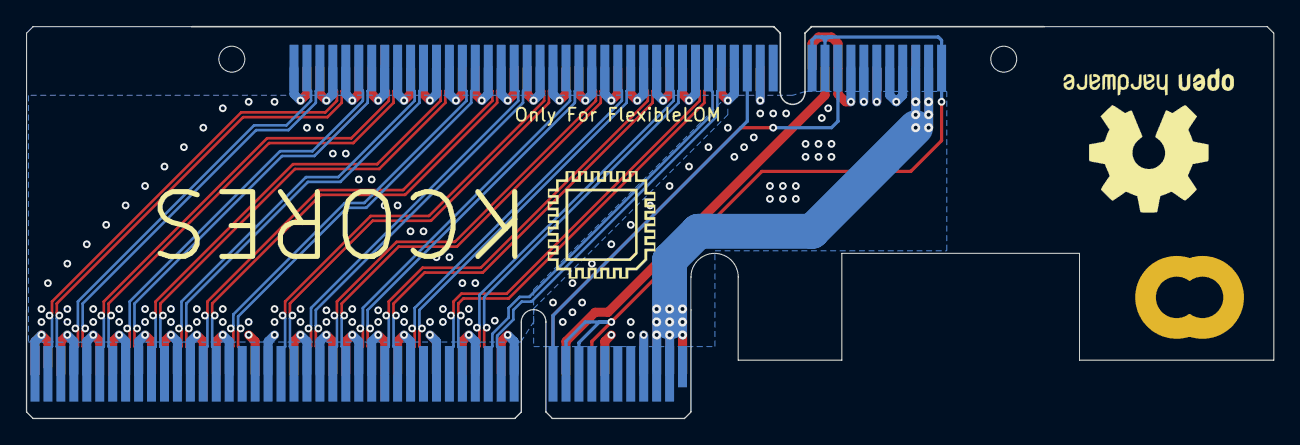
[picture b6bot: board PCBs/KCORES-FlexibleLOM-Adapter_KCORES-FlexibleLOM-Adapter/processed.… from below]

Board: 2 copper layers, 96.3 x 30.2 mm, 5 parts (2 on the bottom side), 40 nets.

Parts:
H1: PCI Card Standard Hole; MountingHole_3.2mm_M3_Pad
H2: Corner Brace Hole; MountingHole_3.2mm_M3_Pad
J1: PCIe_x8; BUS_PCIexpress_x8
J2: HPE_FlexibleLOM; BUS_PCIexpress_x8_Straddle_Mount_Modify
LOGO1: Logo_Open_Hardware_Large; OSHW-Logo2_14.6x12mm_SilkScreen

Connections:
+3V3: J1.A9, J1.A10, J1.B8, J2.A1, J2.A10, J2.A11
+12V: J1.A2, J1.A3, J1.B1, J1.B2, J1.B3, J2.A2, J2.A3, J2.B2, J2.B3
/3V3_AUX: J1.B10, J2.B10
/CLK_N: J1.A14, J2.A17
/CLK_P: J1.A13, J2.A16
/RX0_N: J1.A17, J2.B18
/RX0_P: J1.A16, J2.B17
/RX1_N: J1.A22, J2.B22
/RX1_P: J1.A21, J2.B21
/RX2_N: J1.A26, J2.B26
/RX2_P: J1.A25, J2.B25
/RX3_N: J1.A30, J2.B30
/RX3_P: J1.A29, J2.B29
/RX4_N: J1.A36, J2.B34
/RX4_P: J1.A35, J2.B33
/RX5_N: J1.A40, J2.B38
/RX5_P: J1.A39, J2.B37
/RX6_N: J1.A44, J2.B42
/RX6_P: J1.A43, J2.B41
/RX7_N: J1.A48, J2.B46
/RX7_P: J1.A47, J2.B45
/TX0_N: J1.B15, J2.A20
/TX0_P: J1.B14, J2.A19
/TX1_N: J1.B20, J2.A24
/TX1_P: J1.B19, J2.A23
/TX2_N: J1.B24, J2.A28
/TX2_P: J1.B23, J2.A27
/TX3_N: J1.B28, J2.A32
/TX3_P: J1.B27, J2.A31
/TX4_N: J1.B34, J2.A36
/TX4_P: J1.B33, J2.A35
/TX5_N: J1.B38, J2.A40
/TX5_P: J1.B37, J2.A39
/TX6_N: J1.B42, J2.A44
/TX6_P: J1.B41, J2.A43
/TX7_N: J1.B46, J2.A48
/TX7_P: J1.B45, J2.A47
/nPERST: J1.A11, J2.A14
/nWAKE: J1.B11, J2.A9
GND: J1.A4, J1.A12, J1.A15, J1.A18, J1.A20, J1.A23, J1.A24, J1.A27, J1.A28, J1.A31, J1.A34, J1.A37, J1.A38, J1.A41, J1.A42, J1.A45, J1.A46, J1.A49, J1.B4, J1.B7, J1.B13, J1.B16, J1.B18, J1.B21, J1.B22, J1.B25, J1.B26, J1.B29, J1.B32, J1.B35, J1.B36, J1.B39, J1.B40, J1.B43, J1.B44, J1.B47, J1.B48, J1.B49, J2.A4, J2.A5, J2.A6, J2.A7, J2.A8, J2.A13, J2.A15, J2.A18, J2.A21, J2.A22, J2.A25, J2.A26, J2.A29, J2.A30, J2.A33, J2.A34, J2.A37, J2.A38, J2.A41, J2.A42, J2.A45, J2.A46, J2.A49, J2.B6, J2.B9, J2.B11, J2.B13, J2.B16, J2.B19, J2.B20, J2.B23, J2.B24, J2.B27, J2.B28, J2.B31, J2.B32, J2.B35, J2.B36, J2.B39, J2.B40, J2.B43, J2.B44, J2.B47, J2.B48

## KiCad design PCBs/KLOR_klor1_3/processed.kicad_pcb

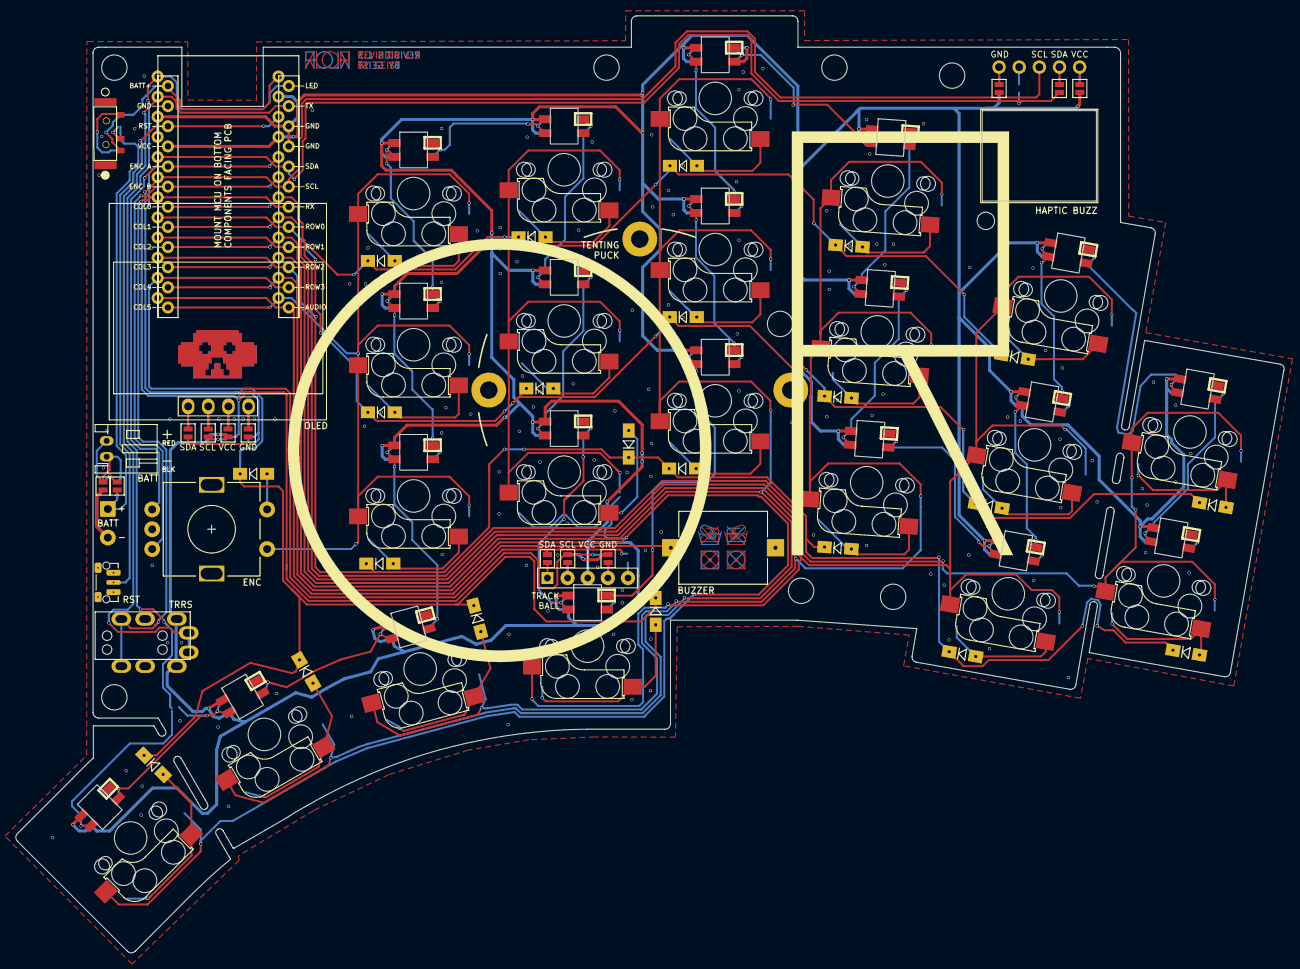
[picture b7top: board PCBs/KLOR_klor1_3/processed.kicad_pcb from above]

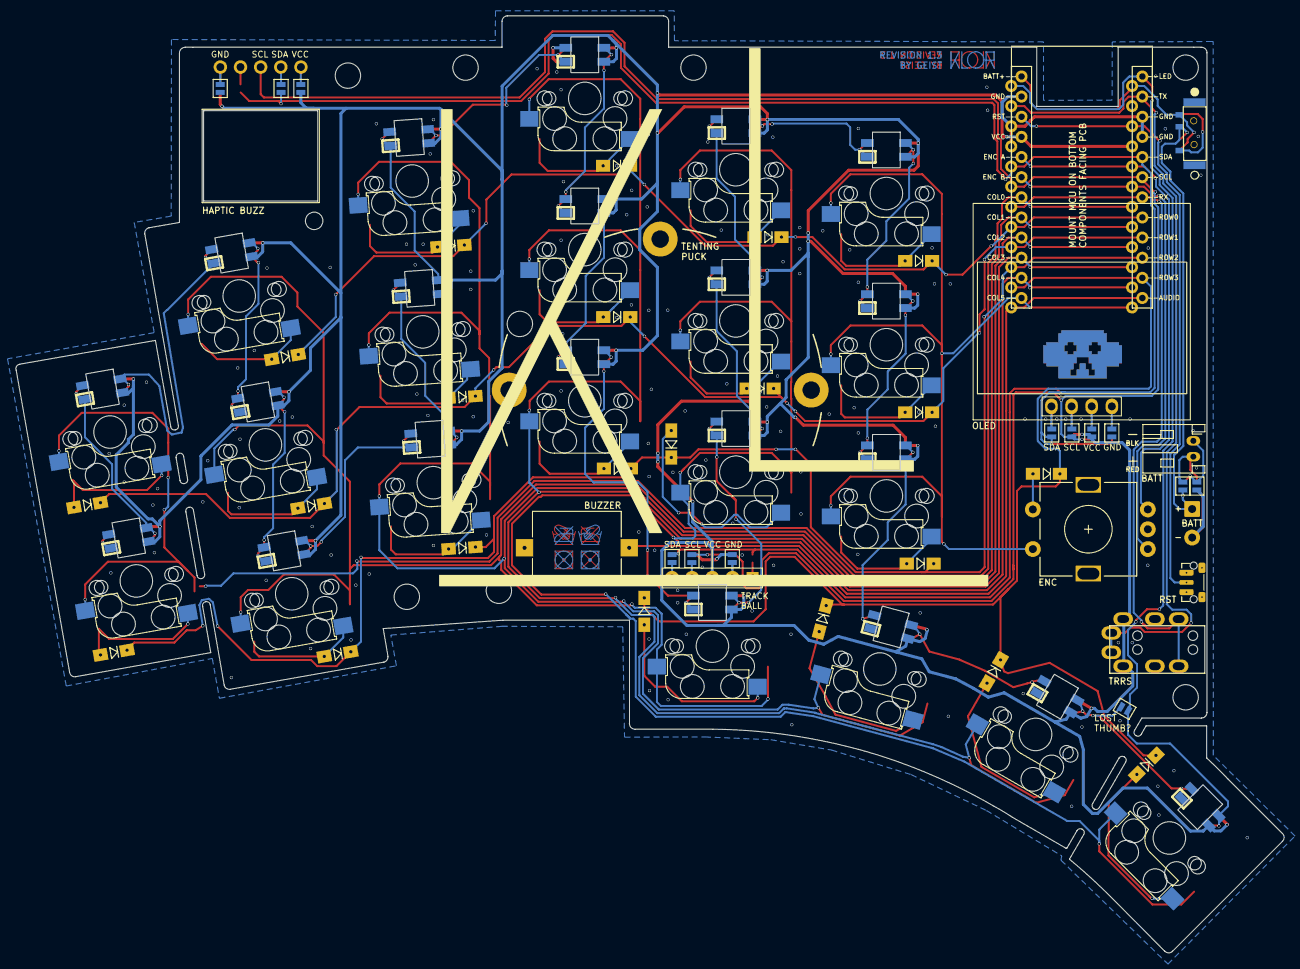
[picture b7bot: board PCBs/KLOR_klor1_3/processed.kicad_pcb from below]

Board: 2 copper layers, 160.0 x 118.2 mm, 88 parts (14 on the bottom side), 79 nets.

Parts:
BT1: JST Connector; JST_PH_reversible
BT2: Battery_Cell; custombatteryconnector_small
BZ1: Buzzer; Buzzer_Mallory_AST1109MLTRQ_reversible
D1, D2, D3, D4, D5, D6, D7, D8, D9, D10, D11, D12, D13, D14, D15, D16, D17, D18, D19, D20, D21, D22: D_Small; Diode_SOD123
J1: MJ-4PP-9
J2: Haptic Buzz; Pimoroni Haptic Buzz DRV2605L Driver
J3: lv27; lvc27_onlyInput
JP1, JP2, JP3, JP4, JP5, JP6, JP7, JP8, JP16, JP17, JP18, JP19, JP20, JP21, JP22, JP23, JP24, JP25, JP26, JP27, JP28: Device_Jumper_NO_Small; Jumper
JP12, JP14: VCC Jumper; Jumper
JP13, JP15: GND Jumper; Jumper
MH1, MH2, MH3, MH4, MH5, MH6, MH7, MH8: MountingHole_3.2mm_M3
MH9: MountingHole_2.2mm_M2
OLED1: SSD1306; SSD1306_128x64OLED
PSW1: SW_DPDT_x2; MSK12C02_reversible
RSW1: SW_Push; SW_Push_1P1T-MP_NO_Horizontal_Alps_SKRTLAE010_both_sides
SW1, SW2, SW3, SW4, SW5, SW6, SW7, SW8, SW9, SW10, SW11, SW12, SW13, SW14, SW15, SW16, SW17, SW19, SW20, SW21, SW22: SW_PUSH-MX_W_LED; SK6812MINI_and_cherry
SW18: RotaryEncoder_Switch; RotaryEncoder_Alps_EC11E-Switch_Vertical_H20mm-keebio_modif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
U1: ProMicro

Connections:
+BATT: PSW1.3 (C), U1.24 (RAW)
/PAD1: BT1.1 (+), JP22.1, JP23.1
/PAD2: BT1.2 (-), JP24.1, JP25.1
/PSW: BT2.1 (+), JP23.2, JP24.2, PSW1.2 (B)
AUDIO: BZ1.1 (-), U1.12 (9/B5)
ENCA: SW18.A, U1.20 (F4/A3)
ENCB: SW18.B, U1.19 (F5/A2)
GND: BT2.2 (-), BZ1.2 (+), J1.2, JP1.2, JP8.2, JP13.1 (A), JP15.1 (A), JP18.2, JP19.2, JP22.2, JP25.2, RSW1.1, SW1.2 (VSS), SW2.2 (VSS), SW3.2 (VSS), SW4.2 (VSS), SW5.2 (VSS), SW6.2 (VSS), SW7.2 (VSS), SW8.2 (VSS), SW9.2 (VSS), SW10.2 (VSS), SW11.2 (VSS), SW12.2 (VSS), SW13.2 (VSS), SW14.2 (VSS), SW15.2 (VSS), SW16.2 (VSS), SW17.2 (VSS), SW18.C, SW19.2 (VSS), SW20.2 (VSS), SW21.2 (VSS), SW22.2 (VSS), U1.3 (GND), U1.4 (GND), U1.23 (GND)
LED: JP26.2, SW19.3 (DIN), U1.1 (TX0/D3)
unnamed: D1.2 (A), SW1.6
unnamed: D2.2 (A), SW2.6
unnamed: D3.2 (A), SW3.6
unnamed: D4.2 (A), SW4.6
unnamed: D5.2 (A), SW5.6
unnamed: D6.2 (A), SW6.6
unnamed: D7.2 (A), SW7.6
unnamed: D8.2 (A), SW8.6
unnamed: D9.2 (A), SW9.6
unnamed: D10.2 (A), SW10.6
unnamed: D11.2 (A), SW11.6
unnamed: D12.2 (A), SW12.6
unnamed: D13.2 (A), SW13.6
unnamed: D14.2 (A), SW14.6
unnamed: D15.2 (A), SW15.6
unnamed: D16.2 (A), SW16.6
unnamed: D17.2 (A), SW17.6
unnamed: D19.2 (A), SW19.6
unnamed: D20.2 (A), SW20.6
unnamed: D21.2 (A), SW21.6
unnamed: D22.2 (A), SW22.6
unnamed: J2.1, JP12.2 (B), JP13.2 (B)
unnamed: J2.2, JP27.2
unnamed: J2.4, JP28.2
unnamed: J2.5, JP14.2 (B), JP15.2 (B)
unnamed: J3.1, JP16.1
unnamed: J3.2, JP17.1, JP19.1
unnamed: J3.4, JP18.1, JP20.1
unnamed: J3.5, JP21.1
unnamed: JP1.1, JP5.1, OLED1.1 (GND)
unnamed: JP2.1, JP6.1, OLED1.2 (VCC)
unnamed: JP3.1, JP7.1, OLED1.3 (SCL)
unnamed: JP4.1, JP8.1, OLED1.4 (SDA)
unnamed: JP26.1, SW19.1 (DOUT), SW20.3 (DIN)
unnamed: SW1.1 (DOUT), SW2.3 (DIN)
unnamed: SW1.3 (DIN), SW6.1 (DOUT)
unnamed: SW2.1 (DOUT), SW7.3 (DIN)
unnamed: SW3.1 (DOUT), SW4.3 (DIN)
unnamed: SW3.3 (DIN), SW8.1 (DOUT)
unnamed: SW4.1 (DOUT), SW9.3 (DIN)
unnamed: SW5.3 (DIN), SW10.1 (DOUT)
unnamed: SW10.3 (DIN), SW16.1 (DOUT)
unnamed: SW11.1 (DOUT), SW17.3 (DIN)
unnamed: SW5.1 (DOUT), SW11.3 (DIN)
unnamed: SW6.3 (DIN), SW12.1 (DOUT)
unnamed: SW12.3 (DIN), SW21.1 (DOUT)
unnamed: SW13.1 (DOUT), SW22.3 (DIN)
unnamed: SW7.1 (DOUT), SW13.3 (DIN)
unnamed: SW8.3 (DIN), SW14.1 (DOUT)
unnamed: SW14.3 (DIN), SW22.1 (DOUT)
unnamed: SW15.1 (DOUT), SW16.3 (DIN)
unnamed: SW9.1 (DOUT), SW15.3 (DIN)
unnamed: SW20.1 (DOUT), SW21.3 (DIN)
RESET: RSW1.2, U1.22 (RST)
RX: J1.3, U1.7 (4/D4)
SCL: J2.3, JP3.2, JP6.2, JP17.2, JP20.2, U1.6 (3/D0/SCL)
SDA: JP4.2, JP5.2, JP16.2, JP21.2, JP27.1, JP28.1, U1.5 (2/D1/SDA)
SW18B: D18.2 (A), SW18.S2
TX: J1.4, U1.2 (RX1/D2)
VCC: J1.1, J3.3, JP2.2, JP7.2, JP12.1 (A), JP14.1 (A), SW1.4 (VDD), SW2.4 (VDD), SW3.4 (VDD), SW4.4 (VDD), SW5.4 (VDD), SW6.4 (VDD), SW7.4 (VDD), SW8.4 (VDD), SW9.4 (VDD), SW10.4 (VDD), SW11.4 (VDD), SW12.4 (VDD), SW13.4 (VDD), SW14.4 (VDD), SW15.4 (VDD), SW16.4 (VDD), SW17.4 (VDD), SW19.4 (VDD), SW20.4 (VDD), SW21.4 (VDD), SW22.4 (VDD), U1.21 (VCC)
col0: SW11.5, SW17.5, U1.18 (F6/A1)
col1: SW5.5, SW10.5, SW16.5, SW22.5, U1.17 (F7/A0)
col2: SW4.5, SW9.5, SW15.5, SW21.5, U1.16 (B1/15)
col3: SW3.5, SW8.5, SW14.5, SW20.5, U1.15 (B3/14)
col4: SW2.5, SW7.5, SW13.5, SW19.5, U1.14 (B2/16)
col5: SW1.5, SW6.5, SW12.5, SW18.S1, U1.13 (B6/10)
row0: D1.1 (K), D2.1 (K), D3.1 (K), D4.1 (K), D5.1 (K), U1.8 (5/C6)
row1: D6.1 (K), D7.1 (K), D8.1 (K), D9.1 (K), D10.1 (K), D11.1 (K), U1.9 (6/D7)
row2: D12.1 (K), D13.1 (K), D14.1 (K), D15.1 (K), D16.1 (K), D17.1 (K), U1.10 (7/E6)
row3: D18.1 (K), D19.1 (K), D20.1 (K), D21.1 (K), D22.1 (K), U1.11 (8/B4)

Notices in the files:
PCBs/Hubble_mcu/processed.kicad_pcb:
CERN OHL-P V2
